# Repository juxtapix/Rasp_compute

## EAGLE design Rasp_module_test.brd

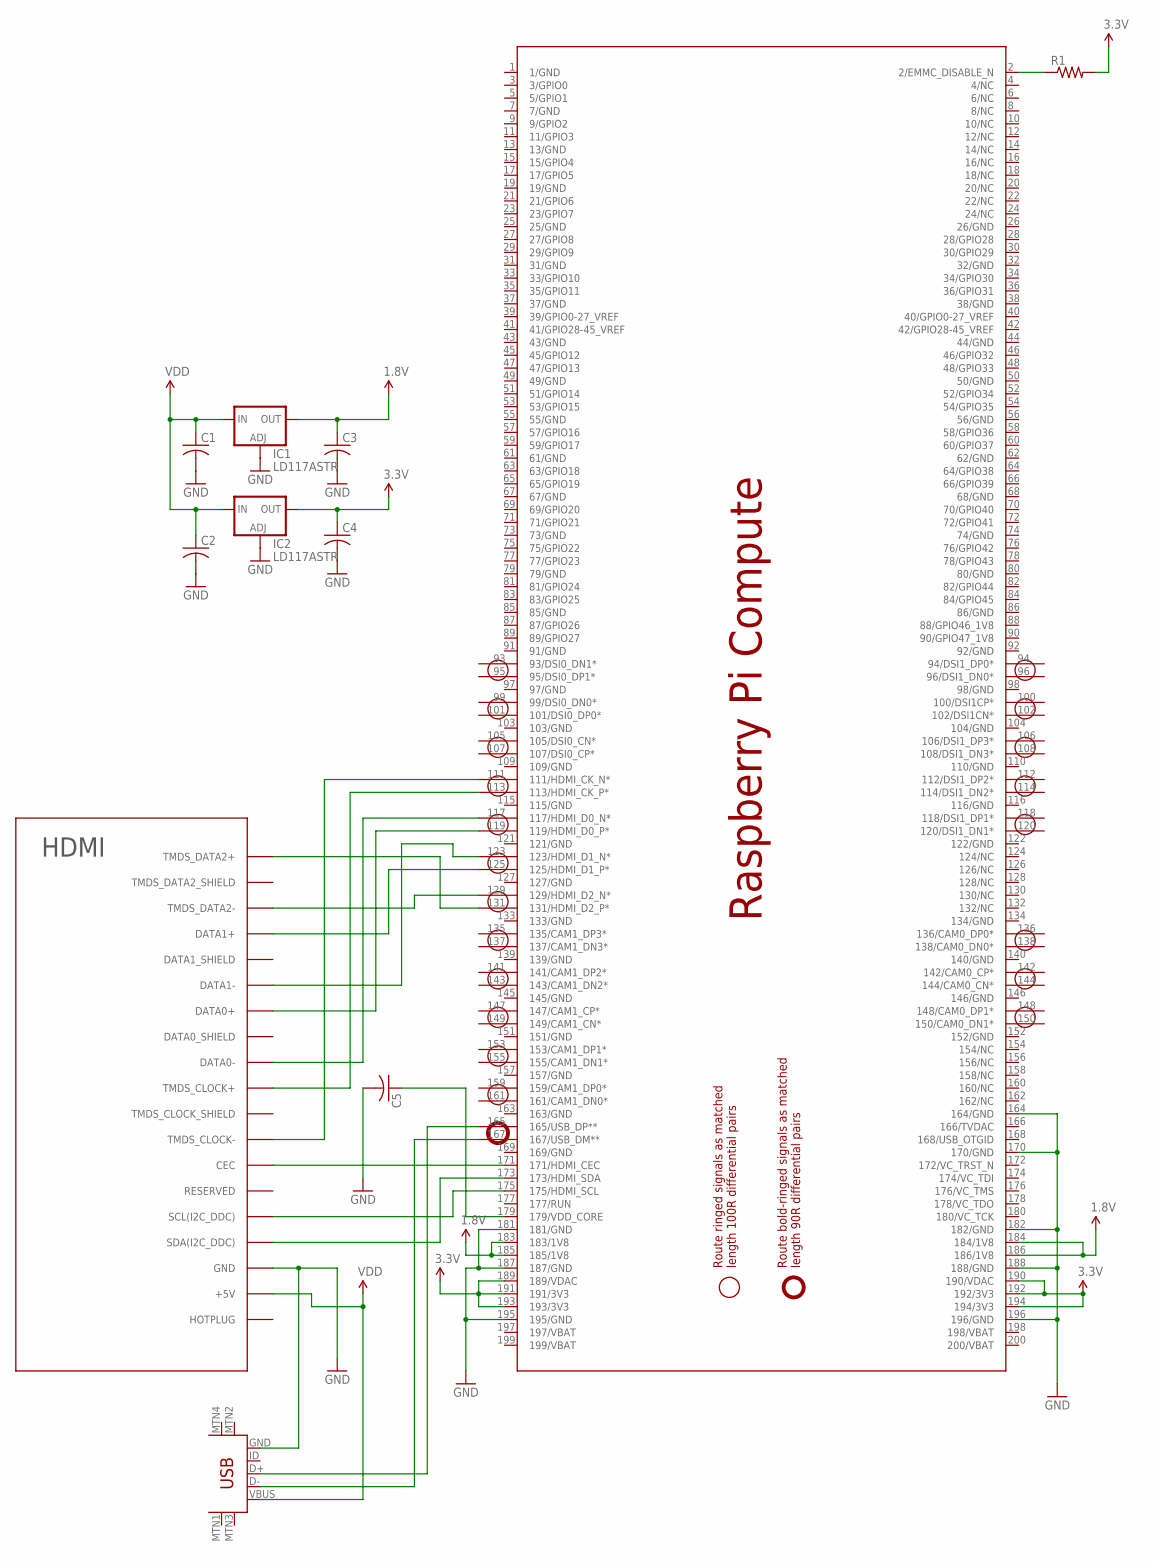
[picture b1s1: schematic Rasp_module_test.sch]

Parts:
C1, C2, C3, C4, C5: C-USC0603; C0603
IC1, IC2: LD117ASTR; SOT223
PCB1: RPI_COMPUTE
R1: RESISTOR0603-RES; 0603-RES
U$1: HDMI
U$2: USB-MINIB-5PIN; USB-MINIB

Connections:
1.8V: C3.1, IC1.4 (OUT), PCB1.183 (183/1V8), PCB1.184 (184/1V8), PCB1.185 (185/1V8), PCB1.186 (186/1V8)
3.3V: C4.1, IC2.4 (OUT), PCB1.189 (189/VDAC), PCB1.190 (190/VDAC), PCB1.191 (191/3V3), PCB1.192 (192/3V3), PCB1.193 (193/3V3), PCB1.194 (194/3V3), R1.2
GND: C1.2, C2.2, C3.2, C4.2, C5.2, IC1.1 (ADJ), IC2.1 (ADJ), PCB1.164 (164/GND), PCB1.170 (170/GND), PCB1.181 (181/GND), PCB1.182 (182/GND), PCB1.187 (187/GND), PCB1.188 (188/GND), PCB1.195 (195/GND), PCB1.196 (196/GND), U$1.P$3 (GND), U$2.GND
unnamed: PCB1.175 (175/HDMI_SCL), U$1.P$5 (SCL(I2C_DDC))
unnamed: PCB1.173 (173/HDMI_SDA), U$1.P$4 (SDA(I2C_DDC))
unnamed: C5.1, PCB1.179 (179/VDD_CORE)
unnamed: PCB1.2 (2/EMMC_DISABLE_N), R1.1
unnamed: PCB1.131 (131/HDMI_D2_P*), U$1.P$19 (TMDS_DATA2+)
unnamed: PCB1.129 (129/HDMI_D2_N*), U$1.P$17 (TMDS_DATA2-)
unnamed: PCB1.125 (125/HDMI_D1_P*), U$1.P$16 (DATA1+)
unnamed: PCB1.123 (123/HDMI_D1_N*), U$1.P$14 (DATA1-)
unnamed: PCB1.119 (119/HDMI_D0_P*), U$1.P$13 (DATA0+)
unnamed: PCB1.117 (117/HDMI_D0_N*), U$1.P$11 (DATA0-)
unnamed: PCB1.113 (113/HDMI_CK_P*), U$1.P$10 (TMDS_CLOCK+)
unnamed: PCB1.111 (111/HDMI_CK_N*), U$1.P$8 (TMDS_CLOCK-)
unnamed: PCB1.165 (165/USB_DP**), U$2.D+
unnamed: PCB1.167 (167/USB_DM**), U$2.D-
unnamed: PCB1.171 (171/HDMI_CEC), U$1.P$7 (CEC)
VDD: C1.1, C2.1, IC1.3 (IN), IC2.3 (IN), U$1.P$2 (+5V), U$2.VBUS

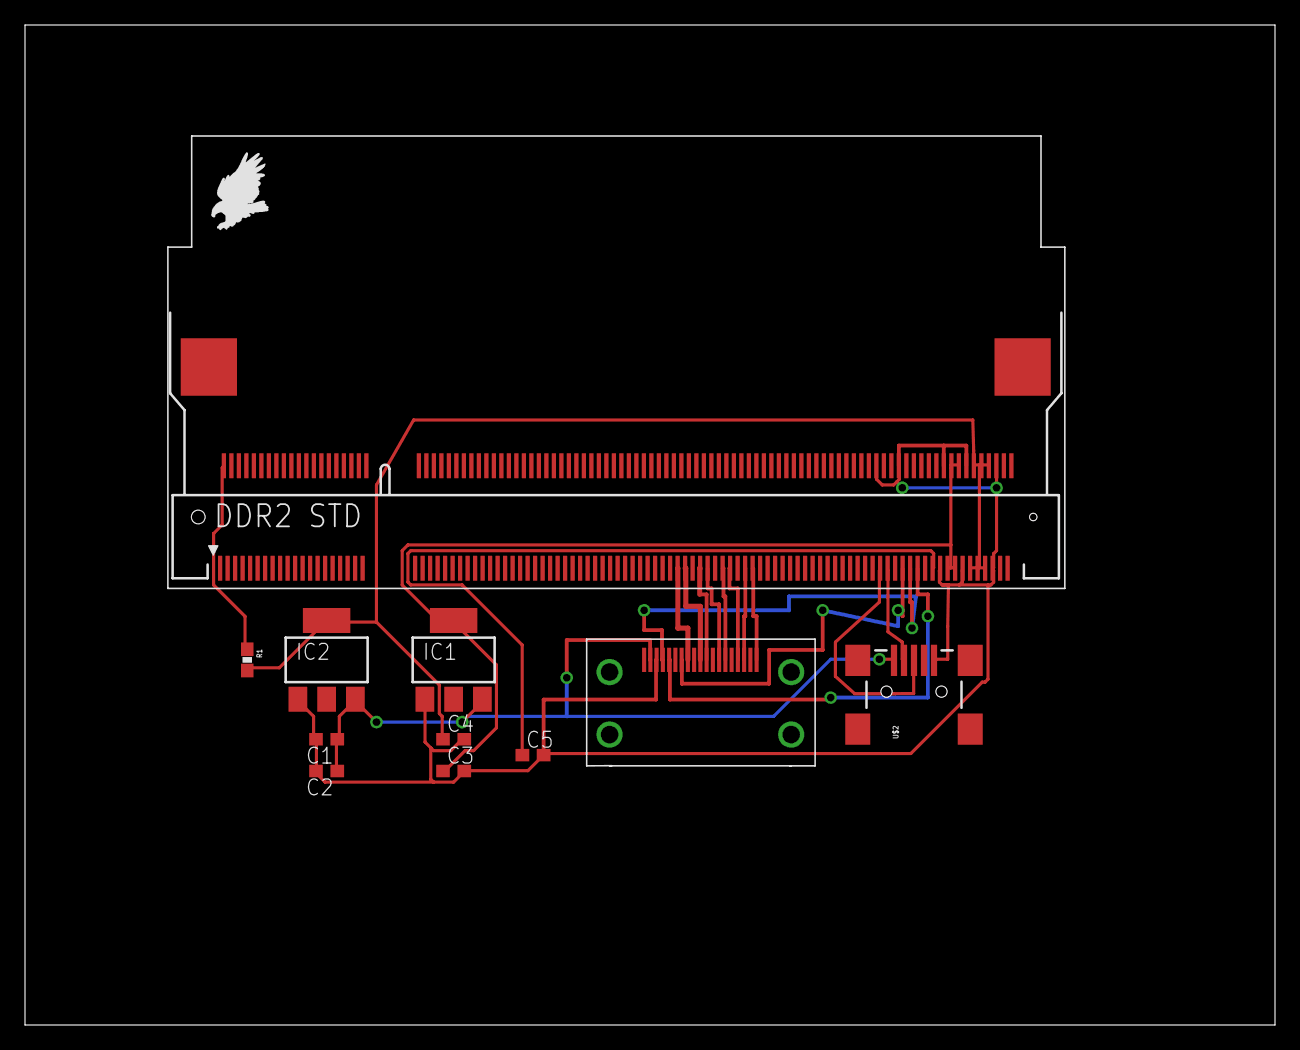
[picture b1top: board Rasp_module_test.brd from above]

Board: 2 copper layers, 100.0 x 80.0 mm, 11 parts (0 on the bottom side), 19 nets.

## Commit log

2015-09-06 initial submission

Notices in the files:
parts and their libraries:
SparkFun-Connectors: Licensing: Creative Commons ShareAlike 4.0 International - https://creativecommons.org/licenses/by-sa/4.0
